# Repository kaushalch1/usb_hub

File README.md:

# Travel USB Hub

A compact usb hub designed for portability and everyday use. This project can make a single usb connection into multiple ports by providing two usb-a ports and one usb-c port, making it a convenient accessory for students and travelers.

## Why did i build it?

modern laptops and chargers often have a limited number of usb ports, requiring users to carry multiple adapters or repeatedly plug and unplug devices.this usb hubb solves this problem by combining multiple USB interfaces into a single pcb.

## Features

- 1 usb-a upstream port for connecting to a host computer
- 2 usb-a downstream ports
- 1 usb-c downstream port
- USB 2.0 data transfer support
- current protection using a schottky diode

## Design Tools
kicad,fusion 360

pcb

schematics

3d model

3d model top panel

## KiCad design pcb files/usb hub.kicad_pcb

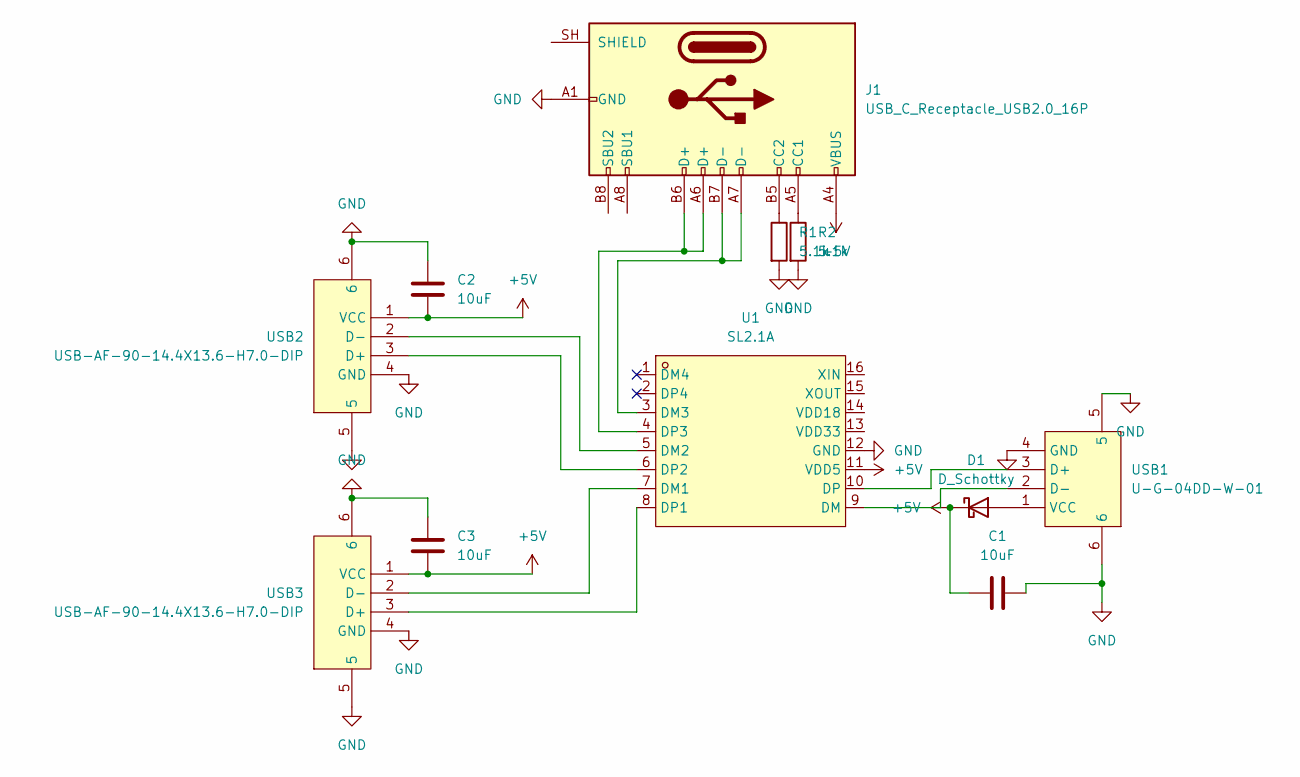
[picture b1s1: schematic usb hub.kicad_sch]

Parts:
C1, C2, C3: 10uF; CP_Elec_4x5.4
D1: D_Schottky; D_2114_3652Metric
J1: USB_C_Receptacle_USB2.0_16P; USB_C_Receptacle_HCTL_HC-TYPE-C-16P-01A
R1, R2: 5.1k; R_0805_2012Metric
U1: SL2.1A; SOP-16_L10.0-W3.9-P1.27-LS6.0-BL; MPN SL2.1A; LCSC Part C192893
USB1: U-G-04DD-W-01; USB-A-TH_U-G-04WD-W-01; MPN U-G-O4DD-W-1; LCSC Part C98125
USB2, USB3: USB-AF-90-14.4X13.6-H7.0-DIP; USB-A-TH_C46407; MPN 903-131A1011D10100; LCSC Part C46407

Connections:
+5V: C1.1, C2.1, C3.1, D1.1 (K), J1.A4 (VBUS), J1.A9 (VBUS), J1.B4 (VBUS), J1.B9 (VBUS), U1.11 (VDD5), USB2.1 (VCC), USB3.1 (VCC)
GND: C1.2, C2.2, C3.2, J1.A1 (GND), J1.A12 (GND), J1.B1 (GND), J1.B12 (GND), R1.2, R2.2, U1.12 (GND), USB1.4 (GND), USB1.5, USB1.6, USB2.4 (GND), USB2.5, USB2.6, USB3.4 (GND), USB3.5, USB3.6
unnamed: D1.2 (A), USB1.1 (VCC)
unnamed: J1.A5 (CC1), R2.1
unnamed: J1.B5 (CC2), R1.1
unnamed: U1.7 (DM1), USB3.2 (D-)
unnamed: U1.5 (DM2), USB2.2 (D-)
unnamed: J1.A7 (D-), J1.B7 (D-), U1.3 (DM3)
unnamed: U1.9 (DM), USB1.2 (D-)
unnamed: U1.8 (DP1), USB3.3 (D+)
unnamed: U1.6 (DP2), USB2.3 (D+)
unnamed: J1.A6 (D+), J1.B6 (D+), U1.4 (DP3)
unnamed: U1.10 (DP), USB1.3 (D+)

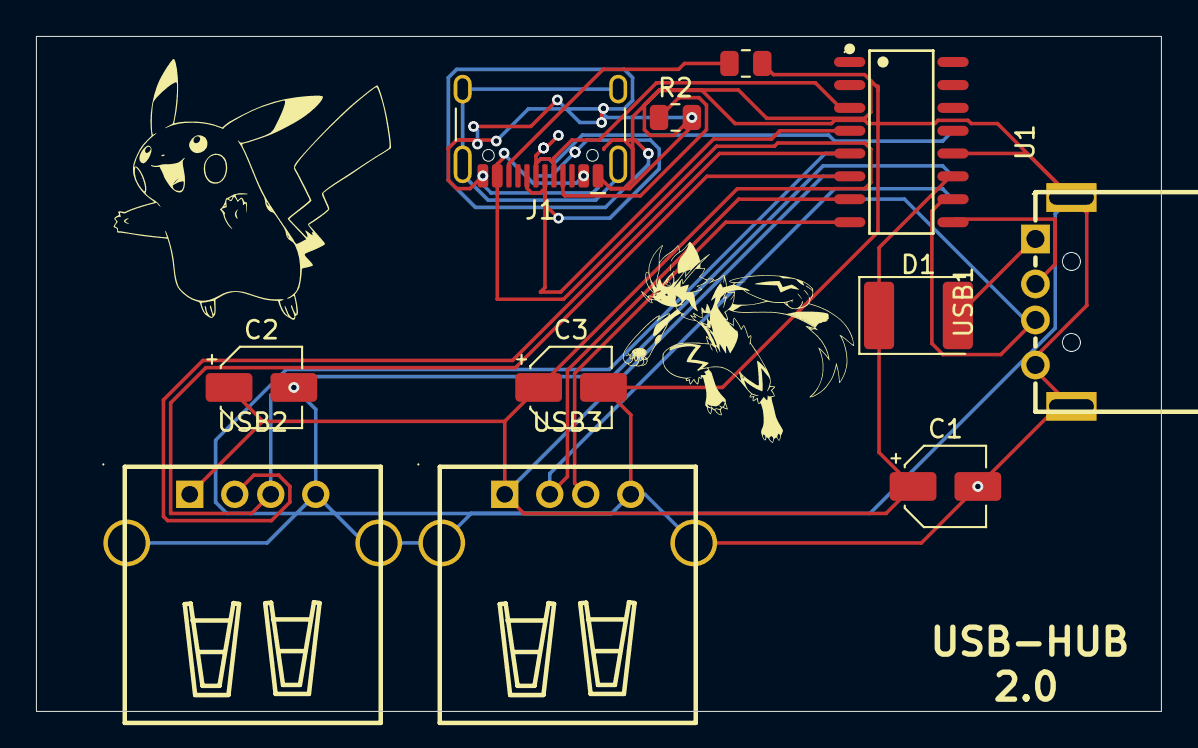
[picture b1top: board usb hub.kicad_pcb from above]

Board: 2 copper layers, 62.5 x 37.5 mm, 11 parts (0 on the bottom side), 13 nets.

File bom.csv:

Reference,Qty / board,Value,Footprint,Part used (MPN),LCSC #,Unit price ($),Price basis,Ext. / board ($),Ext. all boards ($),,
"C1,C2,C3",3,10uF,Capacitor_SMD:CP_Elec_4x5.4,"Chengx RVT1E100M0405 (10uF 25V, 4x5.4)",C81985,$0.0387,10+ tier,$0.1161,$0.58,,
D1,1,D_Schottky,Diode_SMD:D_2114_3652Metric,"Leiditech SS34A (3A 40V Schottky, SMA)",C2759883,$0.0745,5+ list price,$0.0745,$0.37,,
J1,1,USB_C_Receptacle_USB2.0_16P,Connector_USB:USB_C_Receptacle_HCTL_HC-TYPE-C-16P-01A,HCTL HC-TYPE-C-16P-01A-R,C2997433,$0.4827,1+ tier of sibling HC-TYPE-C-16P-01M (C2894899),$0.4827,$2.41,,
"R1,R2",2,5.1k,Resistor_SMD:R_0805_2012Metric,0805 5.1k 1% thick-film,(basic part),$0.0040,100+ tier of same-class 0805 1% parts,$0.0080,$0.04,,
U1,1,SL2.1A,EasyEDA:SOP-16_L10.0-W3.9-P1.27-LS6.0-BL,CoreChips SL2.1A,C192893,$0.2329,5+ tier,$0.2329,$1.16,,
USB1,1,U-G-04DD-W-01,EasyEDA:USB-A-TH_U-G-04WD-W-01,Korean Hroparts U-G-O4DD-W-1,C98125,$0.0687,5+ tier (list $0.088),$0.0687,$0.34,,
"USB2,USB3",2,USB-AF-90-14.4X13.6-H7.0-DIP,EasyEDA:USB-A-TH_C46407,"USB-A female 90deg, white plastic",C46407,$0.0700,Proxy: same-class USB-A TH (C98125 ~ $0.069),$0.1400,$0.70,,
,,,,,,,,,,,
Components total,,,,,,,,$1.12,$5.61,,
PCB fabrication,,,,,,,,$0.40,$2.00,,
PCBA assembly fees,,,,,,,,$5.43,$27.15,,
GRAND TOTAL (excl. shipping & tax),,,,,,,,$6.95,$34.77,,
Boards in this estimate,,,,,,,,,5,,
Cost per assembled board,,,,,,,,,$6.95,,
,,,,,,,,,,,
,,,,,,,,,,,
